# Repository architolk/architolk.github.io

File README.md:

# Architolk

Architolk docs made with [Jekyll](https://jekyllrb.com/)

## Setup

This site runs on Jekyll, an opensource static site generating platform.

- Clone or download a zip of this project to your computer and navigate to the
  project directory in your terminal

> NB: Current versions of github pages works with ruby 3.2.x and Jekyll 3.9.3 ! Make sure you install THESE versions!

- Make sure Ruby is installed, to check if it is, run:
  ```
  ruby -v
  ```
  For more information about installing Ruby, refer to the [Ruby installation ](https://www.ruby-lang.org/en/documentation/installation/).

- Install the Jekyll and bundler [gems](https://jekyllrb.com/docs/ruby-101/#gems) from the commandline:
  ```
  gem install jekyll bundler
  ```
  For more information about installing Jekyll, refer to the [Jekyll quickstart guide](https://jekyllrb.com/docs/quickstart/)

  A specific version of jekyll can be installed via:
  ```
  gem install jekyll -v 3.9.3
  ```

- Some problems may occur if the bundler gem file is updated, but the Gemfile.lock still contains a reference to the old version. This can be solved by:
  ```
  bundle update --bundler
  ```
  Sometimes other gem packages also need to be updated: see the Gemfile for possible updates (like: `bundle update github-pages`).

- Install Gem dependencies for the project by running:
  ```
  bundle install
  ```

- To run the server in your local environment run:
  ```
  bundle exec jekyll serve
  ```

- Go to http://localhost:4000/ in your browser

## Github.io native operation

Nothing is needed! Just make changes to the source, and everything will be published.

The only reason to use a local server and a local build is for testing, it is not necessary for publication on github.io.

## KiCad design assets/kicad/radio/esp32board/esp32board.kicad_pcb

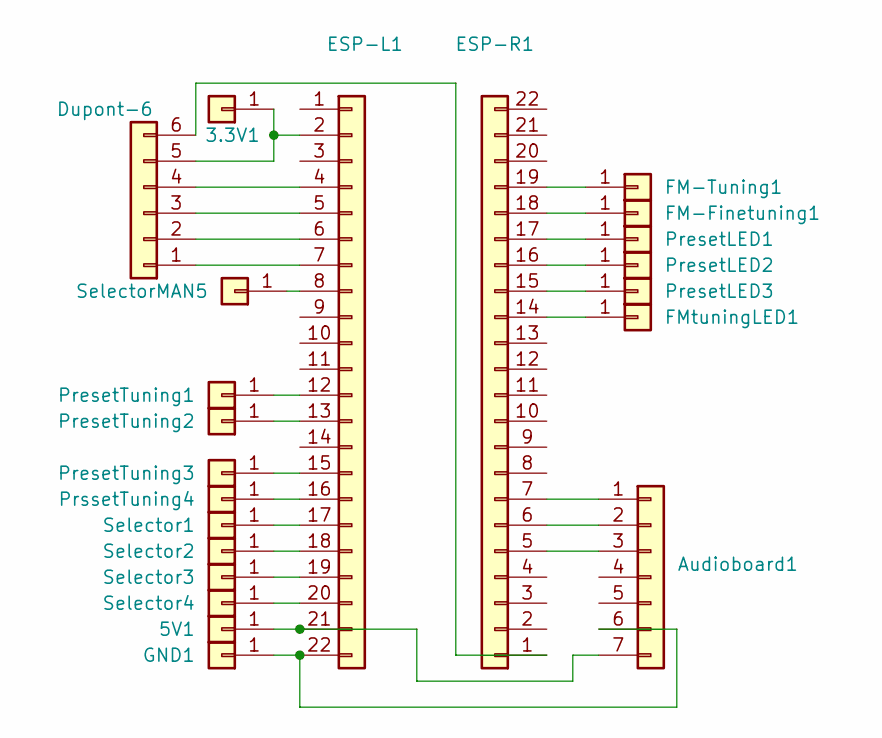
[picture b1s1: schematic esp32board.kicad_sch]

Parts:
3.3V1, 5V1: Conn_01x01; TestPoint_Loop_D1.80mm_Drill1.0mm_Beaded
Audioboard1: Conn_01x07; PinHeader_1x07_P2.54mm_Vertical
Dupont-6: Conn_01x06; PinHeader_1x06_P2.54mm_Vertical
ESP-L1: Conn_01x22; PinHeader_1x22_P2.54mm_Vertical
ESP-R1: Conn_01x22; PinHeader_1x22_P2.54mm_Vertical
FM-Finetuning1: Conn_01x01; TestPoint_Loop_D1.80mm_Drill1.0mm_Beaded
FM-Tuning1: Conn_01x01; TestPoint_Loop_D1.80mm_Drill1.0mm_Beaded
FMtuningLED1: Conn_01x01; TestPoint_Loop_D1.80mm_Drill1.0mm_Beaded
GND1: Conn_01x01; TestPoint_Loop_D1.80mm_Drill1.0mm_Beaded
PresetLED1, PresetLED2, PresetLED3: Conn_01x01; TestPoint_Loop_D1.80mm_Drill1.0mm_Beaded
PresetTuning1, PresetTuning2, PresetTuning3: Conn_01x01; TestPoint_Loop_D1.80mm_Drill1.0mm_Beaded
PrssetTuning4: Conn_01x01; TestPoint_Loop_D1.80mm_Drill1.0mm_Beaded
Selector1, Selector2, Selector3, Selector4: Conn_01x01; TestPoint_Loop_D1.80mm_Drill1.0mm_Beaded
SelectorMAN5: Conn_01x01; TestPoint_Loop_D1.80mm_Drill1.0mm_Beaded

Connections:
unnamed: 3.3V1.1, Dupont-6.5, ESP-L1.2
unnamed: 5V1.1, Audioboard1.7, ESP-L1.21
unnamed: Audioboard1.1, ESP-R1.7
unnamed: Audioboard1.2, ESP-R1.6
unnamed: Audioboard1.3, ESP-R1.5
unnamed: Audioboard1.6, ESP-L1.22, GND1.1
unnamed: Dupont-6.1, ESP-L1.7
unnamed: Dupont-6.2, ESP-L1.6
unnamed: Dupont-6.3, ESP-L1.5
unnamed: Dupont-6.4, ESP-L1.4
unnamed: Dupont-6.6, ESP-R1.1
unnamed: ESP-L1.8, SelectorMAN5.1
unnamed: ESP-L1.12, PresetTuning1.1
unnamed: ESP-L1.13, PresetTuning2.1
unnamed: ESP-L1.15, PresetTuning3.1
unnamed: ESP-L1.16, PrssetTuning4.1
unnamed: ESP-L1.17, Selector1.1
unnamed: ESP-L1.18, Selector2.1
unnamed: ESP-L1.19, Selector3.1
unnamed: ESP-L1.20, Selector4.1
unnamed: ESP-R1.14, FMtuningLED1.1
unnamed: ESP-R1.15, PresetLED3.1
unnamed: ESP-R1.16, PresetLED2.1
unnamed: ESP-R1.17, PresetLED1.1
unnamed: ESP-R1.18, FM-Finetuning1.1
unnamed: ESP-R1.19, FM-Tuning1.1

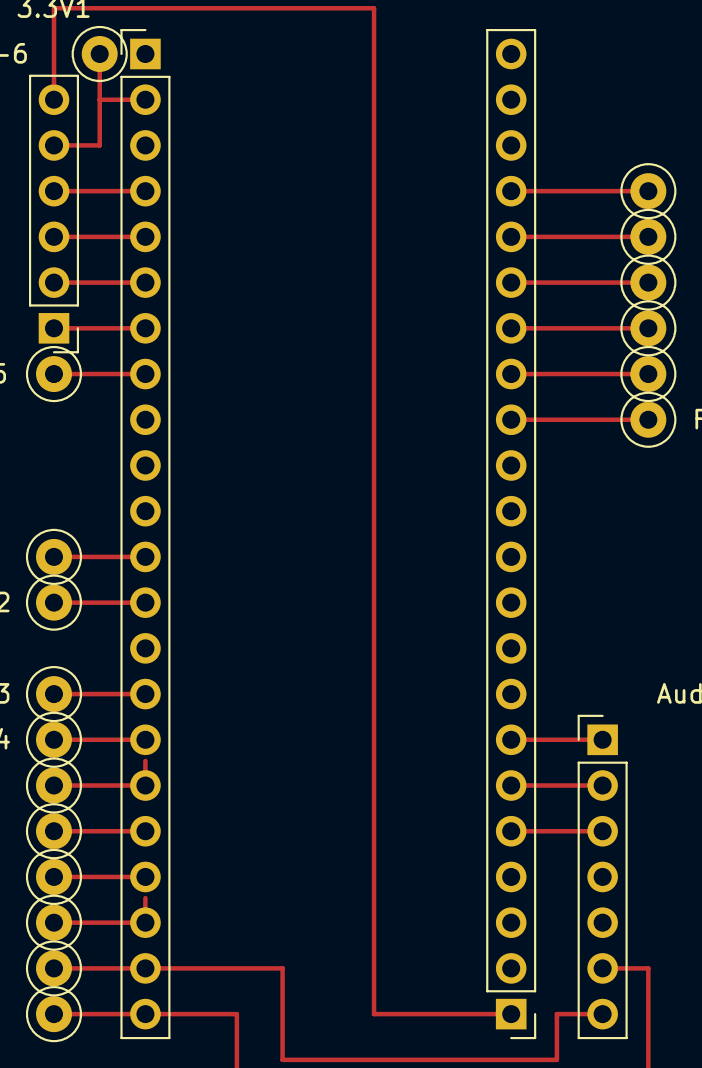
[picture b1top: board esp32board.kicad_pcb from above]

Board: 2 copper layers, 22 parts (0 on the bottom side), 26 nets.

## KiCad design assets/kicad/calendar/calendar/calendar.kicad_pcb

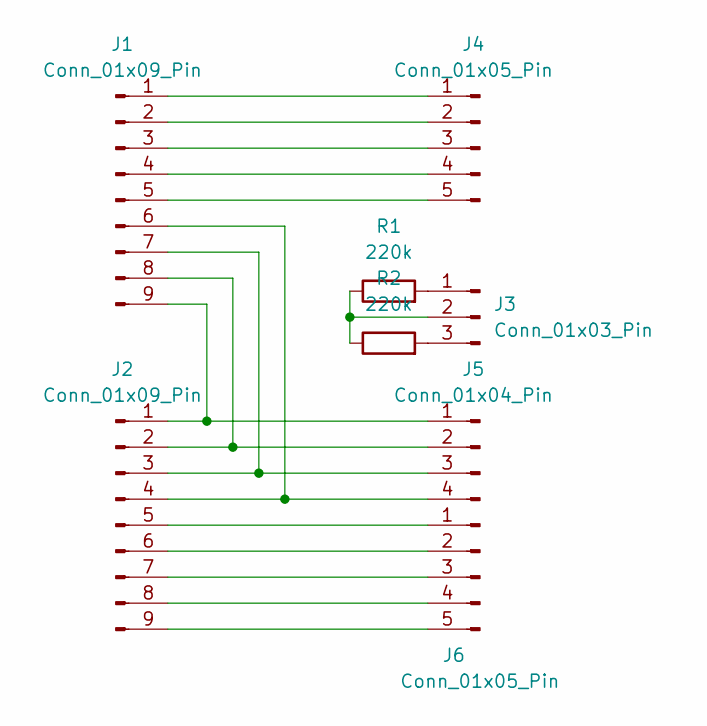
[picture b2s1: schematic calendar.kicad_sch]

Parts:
J1, J2: Conn_01x09_Pin; PinHeader_1x09_P2.54mm_Vertical
J3: Conn_01x03_Pin; PinHeader_1x03_P2.54mm_Vertical
J4, J6: Conn_01x05_Pin; PinHeader_1x05_P2.54mm_Vertical
J5: Conn_01x04_Pin; PinHeader_1x04_P2.54mm_Vertical
R1, R2: 220k; R_Axial_DIN0204_L3.6mm_D1.6mm_P7.62mm_Horizontal

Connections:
unnamed: J1.1, J4.1
unnamed: J1.2, J4.2
unnamed: J1.3, J4.3
unnamed: J1.4, J4.4
unnamed: J1.5, J4.5
unnamed: J1.6, J2.4, J5.4
unnamed: J1.7, J2.3, J5.3
unnamed: J1.8, J2.2, J5.2
unnamed: J1.9, J2.1, J5.1
unnamed: J2.5, J6.1
unnamed: J2.6, J6.2
unnamed: J2.7, J6.3
unnamed: J2.8, J6.4
unnamed: J2.9, J6.5
unnamed: J3.1, R1.2
unnamed: J3.2, R1.1, R2.1
unnamed: J3.3, R2.2

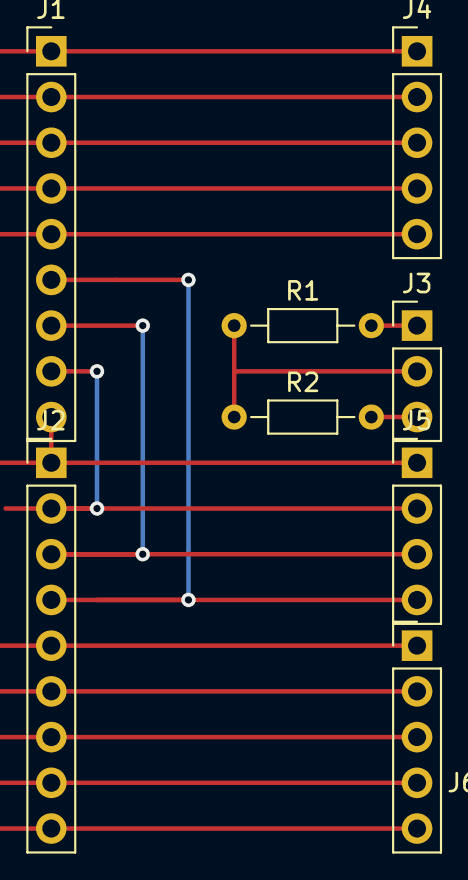
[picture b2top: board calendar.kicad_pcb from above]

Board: 2 copper layers, 8 parts (0 on the bottom side), 17 nets.

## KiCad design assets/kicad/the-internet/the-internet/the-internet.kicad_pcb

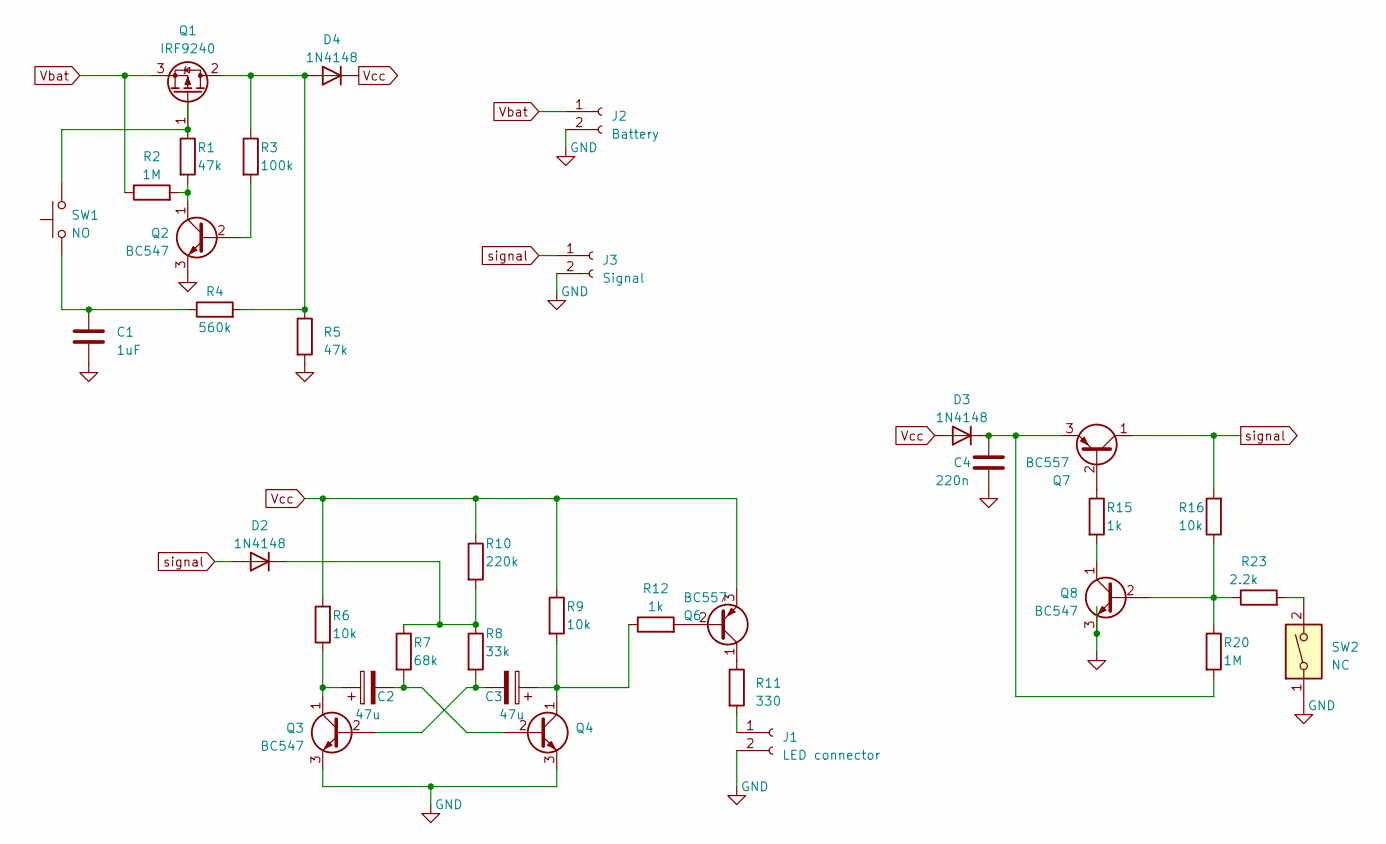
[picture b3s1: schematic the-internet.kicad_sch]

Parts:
C1: 1uF; C_Disc_D3.0mm_W2.0mm_P2.50mm
C2, C3: 47u; CP_Radial_D5.0mm_P2.50mm
C4: 220n; C_Disc_D3.0mm_W2.0mm_P2.50mm
D2, D3, D4: 1N4148; D_DO-35_SOD27_P7.62mm_Horizontal
J1: LED connector; PinHeader_1x02_P2.54mm_Vertical
J2: Battery; PinHeader_1x02_P2.54mm_Vertical
J3: Signal; PinHeader_1x02_P2.54mm_Vertical
Q1: IRF9240; TO-220-3_Vertical
Q2, Q3, Q4, Q8: BC547; TO-92L_Inline_Wide
Q6: BC557; TO-92L_Inline_Wide
Q7: BC557; TO-92_Inline_Wide
R1, R5: 47k; R_Axial_DIN0204_L3.6mm_D1.6mm_P7.62mm_Horizontal
R2, R20: 1M; R_Axial_DIN0204_L3.6mm_D1.6mm_P7.62mm_Horizontal
R3: 100k; R_Axial_DIN0204_L3.6mm_D1.6mm_P7.62mm_Horizontal
R4: 560k; R_Axial_DIN0204_L3.6mm_D1.6mm_P7.62mm_Horizontal
R6, R9, R16: 10k; R_Axial_DIN0204_L3.6mm_D1.6mm_P7.62mm_Horizontal
R7: 68k; R_Axial_DIN0204_L3.6mm_D1.6mm_P7.62mm_Horizontal
R8: 33k; R_Axial_DIN0204_L3.6mm_D1.6mm_P7.62mm_Horizontal
R10: 220k; R_Axial_DIN0204_L3.6mm_D1.6mm_P7.62mm_Horizontal
R11: 330; R_Axial_DIN0204_L3.6mm_D1.6mm_P7.62mm_Horizontal
R12, R15: 1k; R_Axial_DIN0204_L3.6mm_D1.6mm_P7.62mm_Horizontal
R23: 2.2k; R_Axial_DIN0204_L3.6mm_D1.6mm_P7.62mm_Horizontal
SW1: NO; SW_Tactile_SKHH_Angled
SW2: NC; R_Axial_DIN0414_L11.9mm_D4.5mm_P20.32mm_Horizontal

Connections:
GND: C1.2, C4.2, J1.2, J2.2, J3.2, Q2.3 (E), Q3.3 (E), Q4.3 (E), Q8.3 (E), R5.2, SW2.1
unnamed: C1.1, R4.1, SW1.1
unnamed: D2.1 (K), R7.1, R8.1, R10.2
unnamed: C4.1, D3.1 (K), Q7.3 (E), R20.2
unnamed: D4.2 (A), Q1.2 (D), R3.1, R4.2, R5.1
unnamed: J1.1, R11.2
unnamed: Q1.1 (G), R1.1, SW1.2
unnamed: Q2.2 (B), R3.2
unnamed: Q2.1 (C), R1.2, R2.2
unnamed: C3.2, Q3.2 (B), R8.2
unnamed: C2.1, Q3.1 (C), R6.1
unnamed: C2.2, Q4.2 (B), R7.2
unnamed: C3.1, Q4.1 (C), R9.2, R12.1
unnamed: Q6.2 (B), R12.2
unnamed: Q6.1 (C), R11.1
unnamed: Q7.2 (B), R15.1
unnamed: Q8.2 (B), R16.1, R20.1, R23.1
unnamed: Q8.1 (C), R15.2
unnamed: R23.2, SW2.2
Vbat: J2.1, Q1.3 (S), R2.1
Vcc: D3.2 (A), D4.1 (K), Q6.3 (E), R6.2, R9.1, R10.1
signal: D2.2 (A), J3.1, Q7.1 (C), R16.2

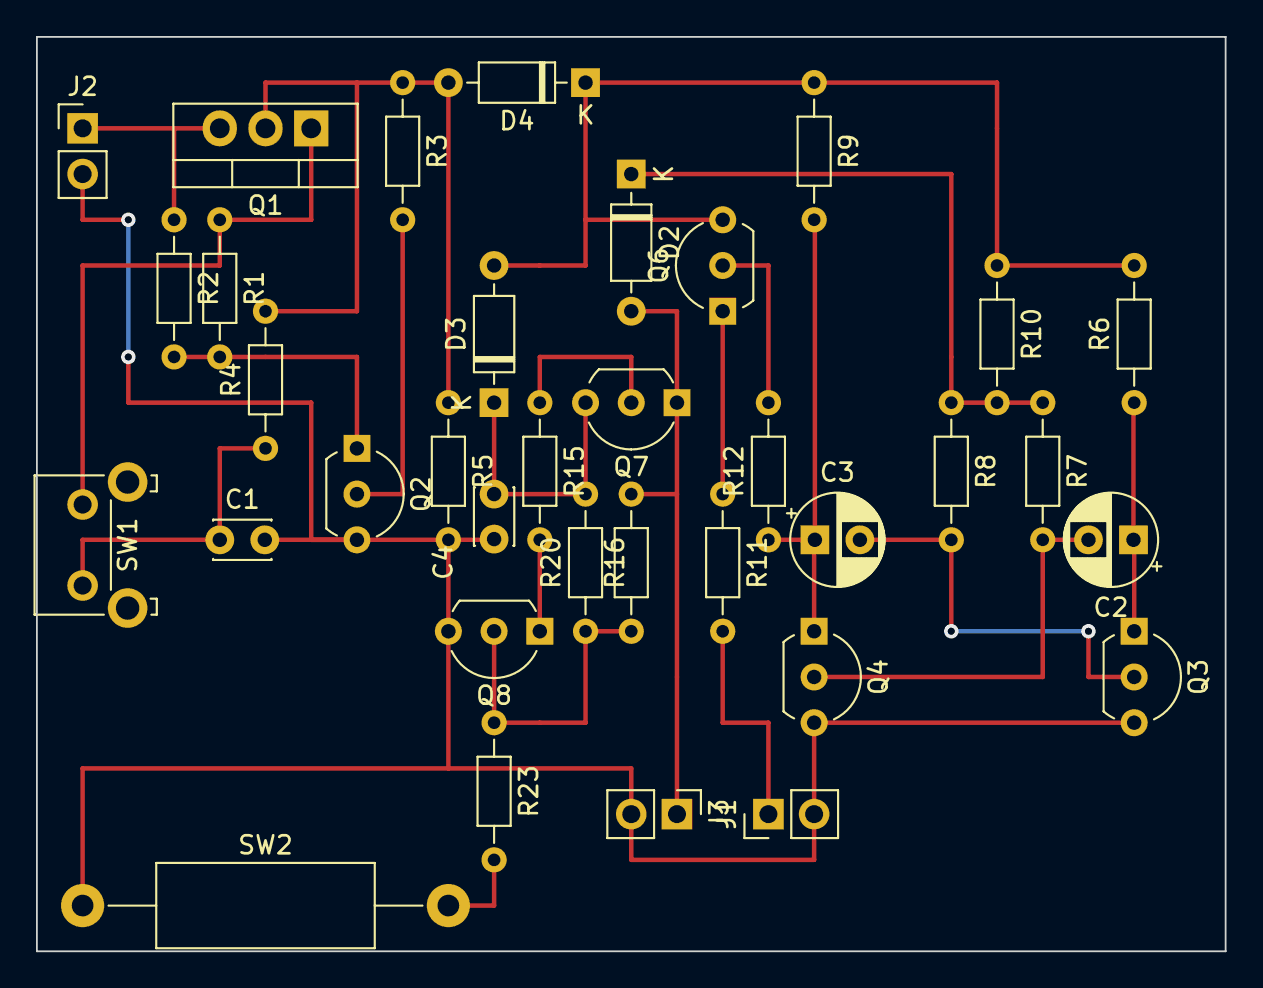
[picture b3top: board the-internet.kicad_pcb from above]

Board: 2 copper layers, 66.0 x 50.8 mm, 35 parts (0 on the bottom side), 22 nets.

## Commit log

2021-03-27 first version
2021-03-27 First working jekyll version
2021-05-02 Version with minimal mistakes layout
2021-05-02 Added some more info
2021-05-08 First version booster
2021-05-08 Added some more content
2021-05-08 Added Pete Cornish reference
2021-05-08 Added booster build page
2021-05-08 Some info on the Ge tranies
2021-05-08 Added some info from old notes
2021-05-08 Added info from notes
2021-05-08 Added build pictures
2021-05-08 Small text change
2021-05-09 Changed front pics
2021-05-09 Some panel info
2021-05-09 Changed feature row feature - test
2021-05-09 Added FM synth files
2021-05-10 Added spice model for PT
2021-05-11 Updated spice model
2021-05-11 Added some calculation info
2021-05-11 Fixed radius
2021-05-12 Added rms and peak to peak calculation
2021-05-12 Added first version PSU circuit
2021-05-12 Added link to spice model
2021-05-13 Added input stage
2021-05-16 Swapped Hi and Lo
2021-05-16 Bump circuit.md
2021-05-16 Fixed link error
2021-05-16 bump
2021-05-18 Added info on triodes and pentodes
2021-05-18 Added another resource
2021-05-19 Some fixes and additions
2021-05-19 Added preamp model data
2021-05-19 Added gain stage
2021-05-21 Added phase inverter circuit
2021-05-22 Added master and cut circuit
2021-05-22 Link fix
2021-05-23 Added output stage
2021-05-24 Added total circuit and fixed some resistor names
2021-05-24 Fixed link
2021-05-24 Added output stage analysis
2021-05-24 Added more calculations for 12ax7
2021-05-25 Added audio
2021-05-25 Added audio sample
2021-05-28 Added load line and power treshold
2021-05-28 Added start of ECC push pull descr
2021-05-28 Added more ECC99 pp info
2021-05-29 Added correct Rk values
2021-05-29 Final figure
2021-05-29 Added some links
2021-05-29 Updated power model page
2021-05-29 Some info on class A vs AB for the power stage
2021-05-30 fixed pics
2021-06-05 Added first description of BJTs
2021-06-13 First version BC549C description
2021-06-13 Added loadline calculation
2021-06-13 Updated standard measurement
2021-06-13 Changed values from calculator
2021-09-03 Added GPIO mapping
2021-10-03 Update of retroloti description
2021-10-10 Added user manual from fm-synth repo
2021-10-16 First test dynamic waveform
2021-10-16 Style different solution
2021-10-16 Next version - with spectrum and js includes
2021-10-16 Add some theory
2021-10-16 Some more info
2021-10-17 Extra resource
2021-10-17 Added sidebands, reactive
2021-10-17 Added new simulator
2021-10-19 Added some theory
2021-10-19 Added some math
2021-10-20 Added feedback math
2021-10-23 Added fm spectrum page
2021-10-23 Added feedback skeleton page
2021-10-23 Skeleton operators page
2021-10-23 Added feedback sim
2021-11-22 Added first part design booster
2021-11-23 small update
2021-11-23 Explained some calculations
2021-12-27 Small addition to inkscape SVG creation
2021-12-27 Fixed load line picture
2021-12-27 Update - correct formulas and values
2021-12-27 Fixed quotient swap
2021-12-27 Added DC equivalent circuit
2021-12-27 New way of calculating stuff
2021-12-28 Included AC analysis
2021-12-28 Added guitar SPICE model
2021-12-28 Updated guitar model
2021-12-28 Added AC128
2021-12-28 Added nav
2021-12-28 Added AC128 image
2021-12-28 Add silicon
2021-12-28 Fixed small error in offset
2021-12-28 Added more Ge BJTs
2021-12-28 Last images
2021-12-28 Fixed nav
2021-12-28 Added plot for OC140
2021-12-28 Booster info added
2021-12-28 Added libs
2021-12-28 Added Darlington Pair as option
2021-12-29 Added frequency curves for boosters
2021-12-29 Added circuit for original tube booster
2021-12-30 Added treble filter calc
2021-12-30 Added case
2021-12-30 Added PCB
2022-01-02 added pcbs
2022-01-02 Added first version banana PCB
2022-01-04 Finished original PCB
2022-01-06 Added BOM complete
2022-01-07 Added link to new knobs
2022-01-07 Added knobs to BOM
2022-01-07 Information about input capacitors
2022-01-10 BOM update
2022-01-10 Checks
2022-01-30 Added full board
2022-01-30 Added full board page
2022-02-05 Added wiring
2022-02-20 Added spring reverb
2022-06-05 Added circuit for full board and updated wiring
2022-06-06 Added Mikrophonie concept
2022-06-13 Update wiring
2022-07-03 Added gain measuring page
2022-07-03 Changed pinout for NPN transistor
2022-07-03 Update with measurements
2022-07-14 Switched input and output
2022-07-15 Fixed PCB
2022-07-15 Added protection diode comment
2022-07-16 Added pinout for dupon connectors
2022-07-16 Updated wiring
2022-07-24 Update to final product
2022-09-10 Added link to github
2022-09-18 Moved vocoder info to github pages
2022-09-19 Added lib for TL071 and lowpass MFB
2022-09-19 Deleted reference to github
2022-09-19 Added vocoder theory introduction
2022-09-21 First overview of components
2022-09-24 Added PSU circuit
2022-10-01 Added some OTA theory
2022-10-02 Added V-to-I converter
2022-10-02 Some more circuits
2022-10-02 Added some formulas
2022-10-02 Added darlington pair buffer circuit
2022-10-09 Small comment on negative rail
2022-10-23 Added EF circuits
2022-12-30 Update description problem
2023-01-13 Added fix for the circuit
2023-02-12 Made design and first version of the case
2023-02-13 Small changes in layout and design
2023-02-17 Added link to 555 timer
2023-02-26 Added Mikrophonie to index
2023-02-26 Small update on vocoder BOM
2023-03-24 Aanvullingen
2023-04-07 Update for latest version of ruby
2023-05-07 First version of the internet
2023-05-08 Added reference to source
2023-05-08 Some comments added to the low-side switching operation
2023-05-08 Some small resistor value changes
2023-05-08 Fixed some resistor values
2023-05-08 Final values
2023-05-12 mosfet analysis and latching
2023-05-12 extra info
2023-05-13 Removed testfiles
2023-05-14 Blinking update, latch update
2023-05-14 Added references
2023-05-14 NE555 circuits
2023-05-14 Small edits
2023-05-16 Added diodes example
2023-05-17 Update latch toggle circuit
2023-05-17 Update basic latch circuit
2023-05-17 Update blinking circuit with LED driver NPN
2023-06-20 Added Oktava MK-12 repair
2023-06-21 Added resource link
2023-06-22 Added replacement parts ids
2023-06-22 Update to circuits
2023-11-08 Added resources
2023-12-27 Uncommitted changes committed
2023-12-27 Added KiCad files for circuit and PCB
2023-12-28 Added signal terminal
2023-12-28 Changed layout for connectors
2023-12-29 Added final version of the internet
2023-12-29 Smoke detector basic files
2023-12-29 Added smoke detector circuit description
2023-12-29 First version calculator
2023-12-30 Added insides
2023-12-31 Update config
2023-12-31 Fixed issue with custom gem
2023-12-31 Added traces
2024-01-01 Added original power circuit
2024-01-02 VFD theory update
2024-01-02 Better description of the vfd operation
2024-01-05 Update VFD pins and datasheets
2024-01-05 Added arduino pins configuration
2024-01-06 Added analysis of original breadboard
2024-01-07 Power calculations update
2024-01-07 some small fixes
2024-01-07 Fixed issue with Vgs
2024-01-09 Update to power management calculations
2024-01-20 Added buck converter
2024-01-21 Added diode text
2024-02-02 Added theremin stuff
2024-02-02 Added theremin resources
2024-02-03 Update for current versions
2024-02-23 Update theremin pages
2025-01-18 Added subwave project
2025-01-26 Added info, upgrade and simplified pdf2svg
2025-02-16 Added descriptions for mutron and oc-2
2025-02-16 Added analyser section
2025-02-16 Subgen circuit added
2025-02-17 Added AD633 and LT1054 description
2025-02-21 square rooting added
2025-02-22 Added peak detector with phase shift
2025-02-23 Added design
2025-03-01 Sign restorer added
2025-06-15 Updated key matrix pinout and connections
2025-06-18 Added new projects
2025-06-19 Added some more info and firmware starting...
2025-06-19 Updated firmware instructions
2025-06-19 Added pin numbers
2025-06-19 Some more pin information
2025-06-20 Added pictures, finished project
2025-06-23 Added hardware configuration for Somfy that worked
2025-06-23 changed pins to include audio and I2C interface
2025-06-23 Add pin config
2025-06-23 Added config info
2025-06-23 Added two more screens
2025-06-24 Added research
2025-06-25 Added last addresses
2025-06-25 Added working test code
2025-06-26 Added group config
2025-06-26 Added resources waveshare + GFX
2025-06-27 Added GFX-library POC
2025-06-27 Added resources, small change in pin assignment
2025-06-28 Added weerlive API desc
2025-06-28 Added weather font
2025-07-05 Pin assignment final, PCB for connections
2025-07-05 breakout board added
2025-07-08 Added calendar icons
2025-07-11 Updated project info
2025-07-14 Added lipo battery curve resource
2025-12-17 Added documentation for ROVA api
2026-02-19 Added geomatron first version
2026-02-24 Added more info
2026-02-25 Added color chords
2026-04-08 Update nav
2026-04-17 Update phantom power
2026-04-17 Added circuit for charge amp
2026-04-17 Added comment regarding bode plot
2026-04-19 added noise boxes examples
2026-04-19 Added more examples
2026-04-24 Extra link for 3-wire piezo buzzer
2026-05-23 Added radio project
2026-05-25 Adding user manual
2026-05-25 Small changes
2026-05-26 Added upload webpage
2026-05-27 Update fine tuning
2026-05-27 Added link to code and hint for easter egg mode
2026-06-06 Added link to explanation of calculator keys
2026-06-06 Added keys gloassary
